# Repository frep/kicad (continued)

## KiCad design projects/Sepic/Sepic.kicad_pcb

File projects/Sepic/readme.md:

Sepic
=====

A Single Ended Primary Inductance Converter based on the LT1370.

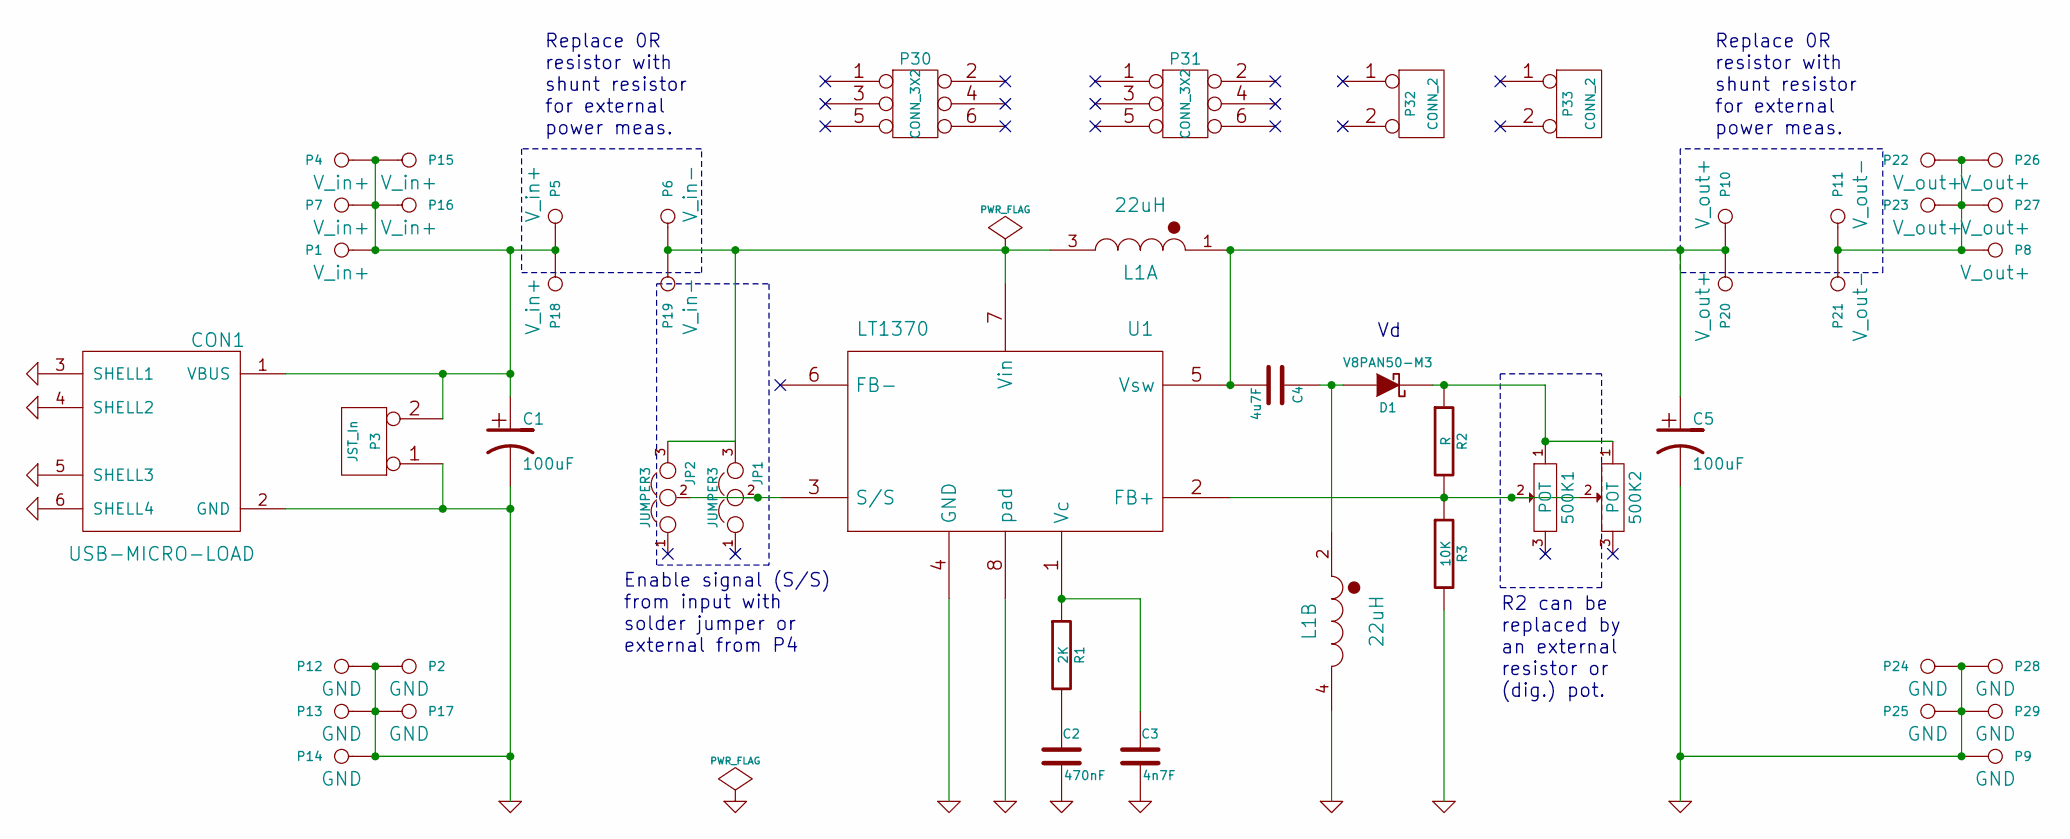
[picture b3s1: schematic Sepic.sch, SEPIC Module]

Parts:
500K1, 500K2: POT; Trimmer
C1, C5: 100uF; Cap_Nichicon
C2: 470nF; C0805
C3: 4n7F; C0805
C4: 4u7F; R1206
CON1: USB-MICRO-LOAD; USB_Micro_Load
D1: V8PAN50-M3; DO-221BC
JP1, JP2: JUMPER3; Pin_Proto_Straight_1x03
L1: 22uH; InductorsCoupled
P1: V_in+; SMD_SOLDERPOINT
P2, P12, P13, P17, P24, P25, P28, P29: GND; Pin_Proto_Straight_1x01
P3: JST_In; JST-PH-2-THM-RA
P4, P5, P7, P15, P16, P18: V_in+; Pin_Proto_Straight_1x01
P6, P19: V_in-; Pin_Proto_Straight_1x01
P8: V_out+; SMD_SOLDERPOINT
P9, P14: GND; SMD_SOLDERPOINT
P10, P20, P22, P23, P26, P27: V_out+; Pin_Proto_Straight_1x01
P11, P21: V_out-; Pin_Proto_Straight_1x01
P30, P31: CONN_3X2; Pin_Proto_Straight_2x03
P32, P33: CONN_2; Pin_Proto_Straight_1x02
R1: 2K; R0805
R2: R; R0805
R3: 10K; R0805
U1: LT1370; TO-263-7

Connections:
GND: C1.2, C2.2, C3.2, C5.2, CON1.2 (GND), CON1.3 (SHELL1), CON1.4 (SHELL2), CON1.5 (SHELL3), CON1.6 (SHELL4), L1.4, P2.1, P3.1, P9.1, P12.1, P13.1, P14.1, P17.1, P24.1, P25.1, P28.1, P29.1, R3.2, U1.4 (GND), U1.8 (pad)
unnamed: 500K1.1, 500K2.1, D1.2 (K), R2.1
unnamed: 500K1.2, 500K2.2, R2.2, R3.1, U1.2 (FB+)
unnamed: C1.1, CON1.1 (VBUS), P1.1, P3.2 (PM), P4.1, P5.1, P7.1, P15.1, P16.1, P18.1
unnamed: C2.1, R1.2
unnamed: C3.1, R1.1, U1.1 (Vc)
unnamed: C4.1, D1.1 (A), L1.2
unnamed: C4.2, C5.1, L1.1, P10.1, P20.1, U1.5 (Vsw)
unnamed: JP1.2, JP2.2, U1.3 (S/S)
unnamed: JP1.3, JP2.3, L1.3, P6.1, P19.1, U1.7 (Vin)
unnamed: P8.1, P11.1, P21.1, P22.1, P23.1, P26.1, P27.1

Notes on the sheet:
Enable signal (S/S) from input with solder jumper or external from P4
R2 can be replaced by an external resistor or (dig.) pot.
Replace 0R resistor with shunt resistor for external power meas.

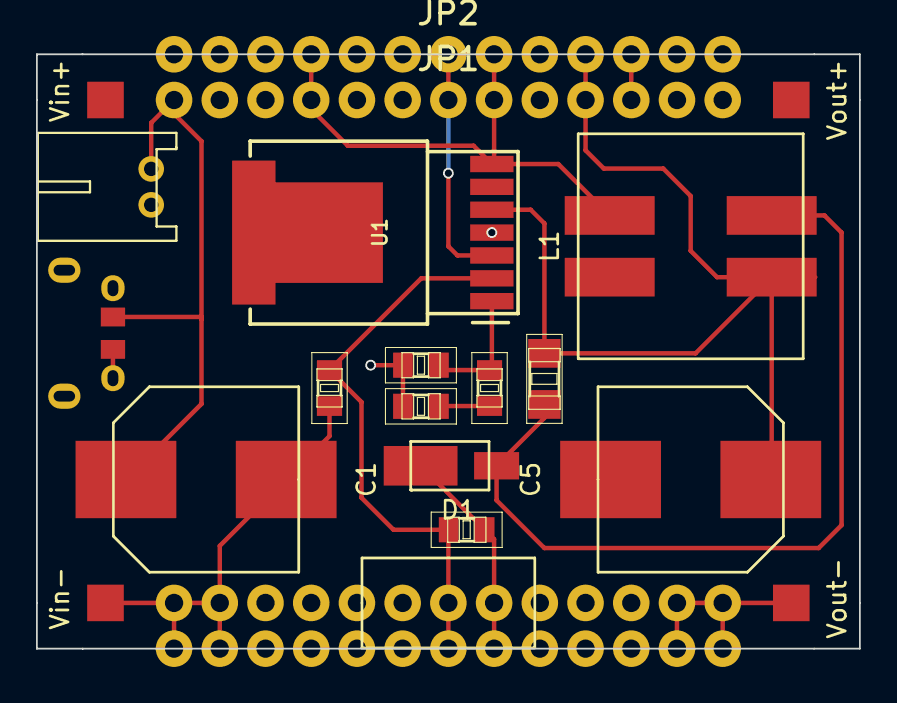
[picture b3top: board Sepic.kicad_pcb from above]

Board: 2 copper layers, 45.7 x 33.0 mm, 49 parts (0 on the bottom side), 11 nets.

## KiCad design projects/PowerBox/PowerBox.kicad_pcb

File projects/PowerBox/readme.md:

PowerBox
========
description is following soon...

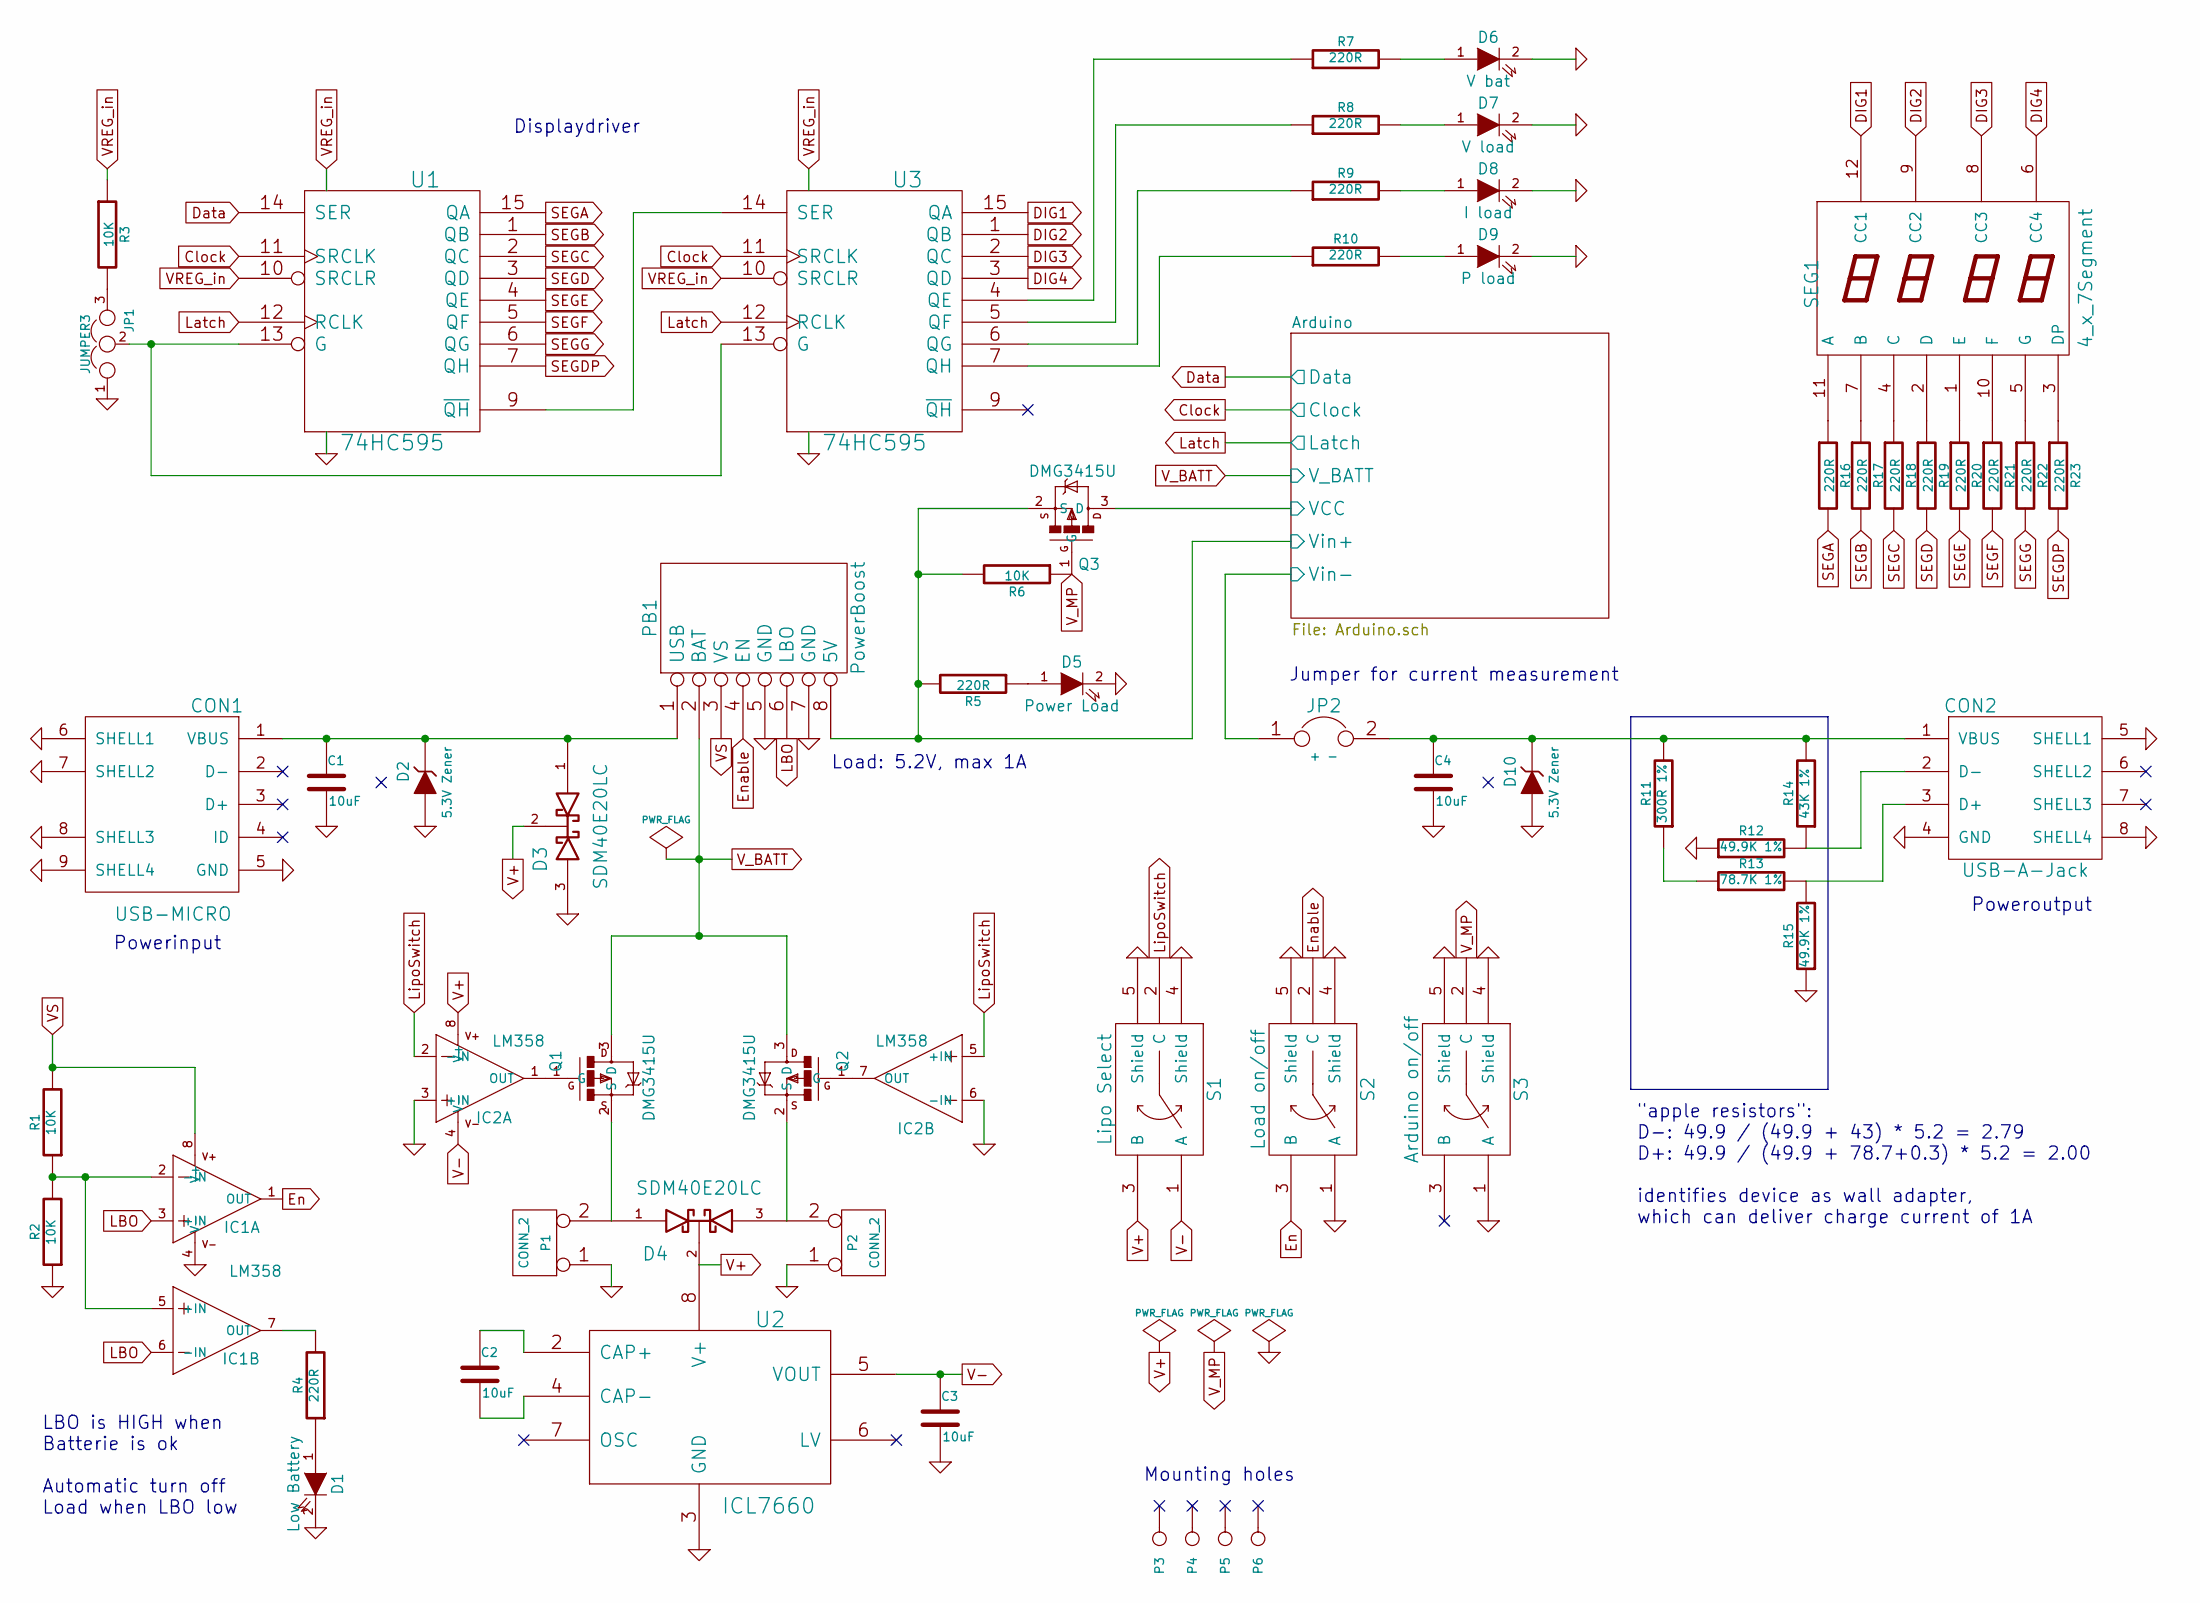
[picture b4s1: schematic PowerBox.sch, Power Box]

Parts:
C1, C2, C3, C4: 10uF; C0805
CON1: USB-MICRO; USB_Micro
CON2: USB-A-Jack
D1: Low Battery; LED-0805
D2, D10: 5.3V Zener; SOT23
D3, D4: SDM40E20LC; SOT23
D5: Power Load; LED-0805
D6: V bat; LED-0805
D7: V load; LED-0805
D8: I load; LED-0805
D9: P load; LED-0805
IC1, IC2: LM358; SOIC8
JP1: JUMPER3; Pin_Proto_Straight_1x03
JP2: + -; Pin_Proto_Straight_1x02
P1, P2: CONN_2; JST-PH-2-THM
P3, P4, P5, P6: CONN_1; MountingHole_3mm
PB1: PowerBoost; Powerboost1000C
Q1, Q2, Q3: DMG3415U; SOT23
R1, R2, R3, R6: 10K; R0805
R4, R5, R7, R8, R9, R10, R16, R17, R18, R19, R20, R21, R22, R23: 220R; R0805
R11: 300R 1%; R0805
R12, R15: 49.9K 1%; R0805
R13: 78.7K 1%; R0805
R14: 43K 1%; R0805
S1: Lipo Select; Switch_SPDT
S2: Load on/off; Switch_SPDT
S3: Arduino on/off; Switch_SPDT
SEG1: 4_x_7Segment; 4digit7segment
U1, U3: 74HC595; SO16
U2: ICL7660; SOIC8

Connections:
/Arduino/VCC: Q3.3 (D); also elsewhere on the board
/Arduino/Vin+: PB1.8 (5V), Q3.2 (S), R5.2, R6.2; also elsewhere on the board
/Arduino/Vin-: JP2.1; also elsewhere on the board
D7: U1.11 (SRCLK), U3.11 (SRCLK); also elsewhere on the board
DIG1: SEG1.12 (CC1), U3.15 (QA)
DIG2: SEG1.9 (CC2), U3.1 (QB)
DIG3: SEG1.8 (CC3), U3.2 (QC)
DIG4: SEG1.6 (CC4), U3.3 (QD)
En: IC1.1 (OUT), S2.3 (B)
Enable: PB1.4 (EN), S2.2 (C)
GND: C1.2, C3.2, C4.2, CON1.5 (GND), CON1.6 (SHELL1), CON1.7 (SHELL2), CON1.8 (SHELL3), CON1.9 (SHELL4), CON2.4 (GND), CON2.5 (SHELL1), CON2.8 (SHELL4), D1.2 (K), D2.1 (A), D3.3 (cathode), D5.2 (K), D6.2 (K), D7.2 (K), D8.2 (K), D9.2 (K), D10.1 (A), IC1.4 (V-), IC2.3 (+IN), IC2.6 (-IN), JP1.1, P1.1, P2.1, PB1.5 (GND), PB1.7 (GND), R2.1, R12.1, R15.1, S1.4 (Shield), S1.5 (Shield), S2.1 (A), S2.4 (Shield), S2.5 (Shield), S3.1 (A), S3.4 (Shield), S3.5 (Shield), U1.8 (GND), U2.3 (GND), U3.8 (GND); also elsewhere on the board
IO_11: U1.12 (RCLK), U3.12 (RCLK); also elsewhere on the board
IO_12: U1.14 (SER); also elsewhere on the board
LBO: IC1.3 (+IN), IC1.6 (-IN), PB1.6 (LBO)
LipoSwitch: IC2.2 (-IN), IC2.5 (+IN), S1.2 (C)
unnamed: C1.1, CON1.1 (VBUS), D2.3 (K), D3.1 (Anode), PB1.1 (USB)
unnamed: C2.1, U2.2 (CAP+)
unnamed: C2.2, U2.4 (CAP-)
unnamed: C4.1, CON2.1 (VBUS), D10.3 (K), JP2.2, R11.2, R14.2
unnamed: CON2.2 (D-), R12.2, R14.1
unnamed: CON2.3 (D+), R13.2, R15.2
unnamed: D1.1 (A), R4.1
unnamed: D4.1 (Anode), P1.2 (PM), Q1.2 (S)
unnamed: D4.3 (cathode), P2.2 (PM), Q2.2 (S)
unnamed: D5.1 (A), R5.1
unnamed: D6.1 (A), R7.2
unnamed: D7.1 (A), R8.2
unnamed: D8.1 (A), R9.2
unnamed: D9.1 (A), R10.2
unnamed: IC1.2 (-IN), IC1.5 (+IN), R1.1, R2.2
unnamed: IC1.7 (OUT), R4.2
unnamed: IC2.1 (OUT), Q1.1 (G)
unnamed: IC2.7 (OUT), Q2.1 (G)
unnamed: JP1.2, U1.13 (G), U3.13 (G)
unnamed: JP1.3, R3.2
unnamed: R7.1, U3.4 (QE)
unnamed: R8.1, U3.5 (QF)
unnamed: R9.1, U3.6 (QG)
unnamed: R10.1, U3.7 (QH)
unnamed: R11.1, R13.1
unnamed: R16.1, SEG1.11 (A)
unnamed: R17.1, SEG1.7 (B)
unnamed: R18.1, SEG1.4 (C)
unnamed: R19.1, SEG1.2 (D)
unnamed: R20.1, SEG1.1 (E)
unnamed: R21.1, SEG1.10 (F)
unnamed: R22.1, SEG1.5 (G)
unnamed: R23.1, SEG1.3 (DP)
unnamed: U1.9 (~QH), U3.14 (SER)
SEGA: R16.2, U1.15 (QA)
SEGB: R17.2, U1.1 (QB)
SEGC: R18.2, U1.2 (QC)
SEGD: R19.2, U1.3 (QD)
SEGDP: R23.2, U1.7 (QH)
SEGE: R20.2, U1.4 (QE)
SEGF: R21.2, U1.5 (QF)
SEGG: R22.2, U1.6 (QG)
V+: D3.2 (AK), D4.2 (AK), IC2.8 (V+), S1.3 (B), U2.8 (V+)
V-: C3.1, IC2.4 (V-), S1.1 (A), U2.5 (VOUT)
VREG_in: R3.1, U1.10 (SRCLR), U1.16 (VCC), U3.10 (SRCLR), U3.16 (VCC); also elsewhere on the board
VS: IC1.8 (V+), PB1.3 (VS), R1.2
V_BATT: PB1.2 (BAT), Q1.3 (D), Q2.3 (D); also elsewhere on the board
V_MP: Q3.1 (G), R6.1, S3.2 (C)

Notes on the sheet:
Powerinput
Poweroutput
Mounting holes
"apple resistors": D-: 49.9 / (49.9 + 43) * 5.2 = 2.79 D+: 49.9 / (49.9 + 78.7+0.3) * 5.2 = 2.00 identifies device as wall adapter, which can deliver charge current of 1A
LBO is HIGH when Batterie is ok Automatic turn off Load when LBO low
Jumper for current measurement
Displaydriver
Load: 5.2V, max 1A

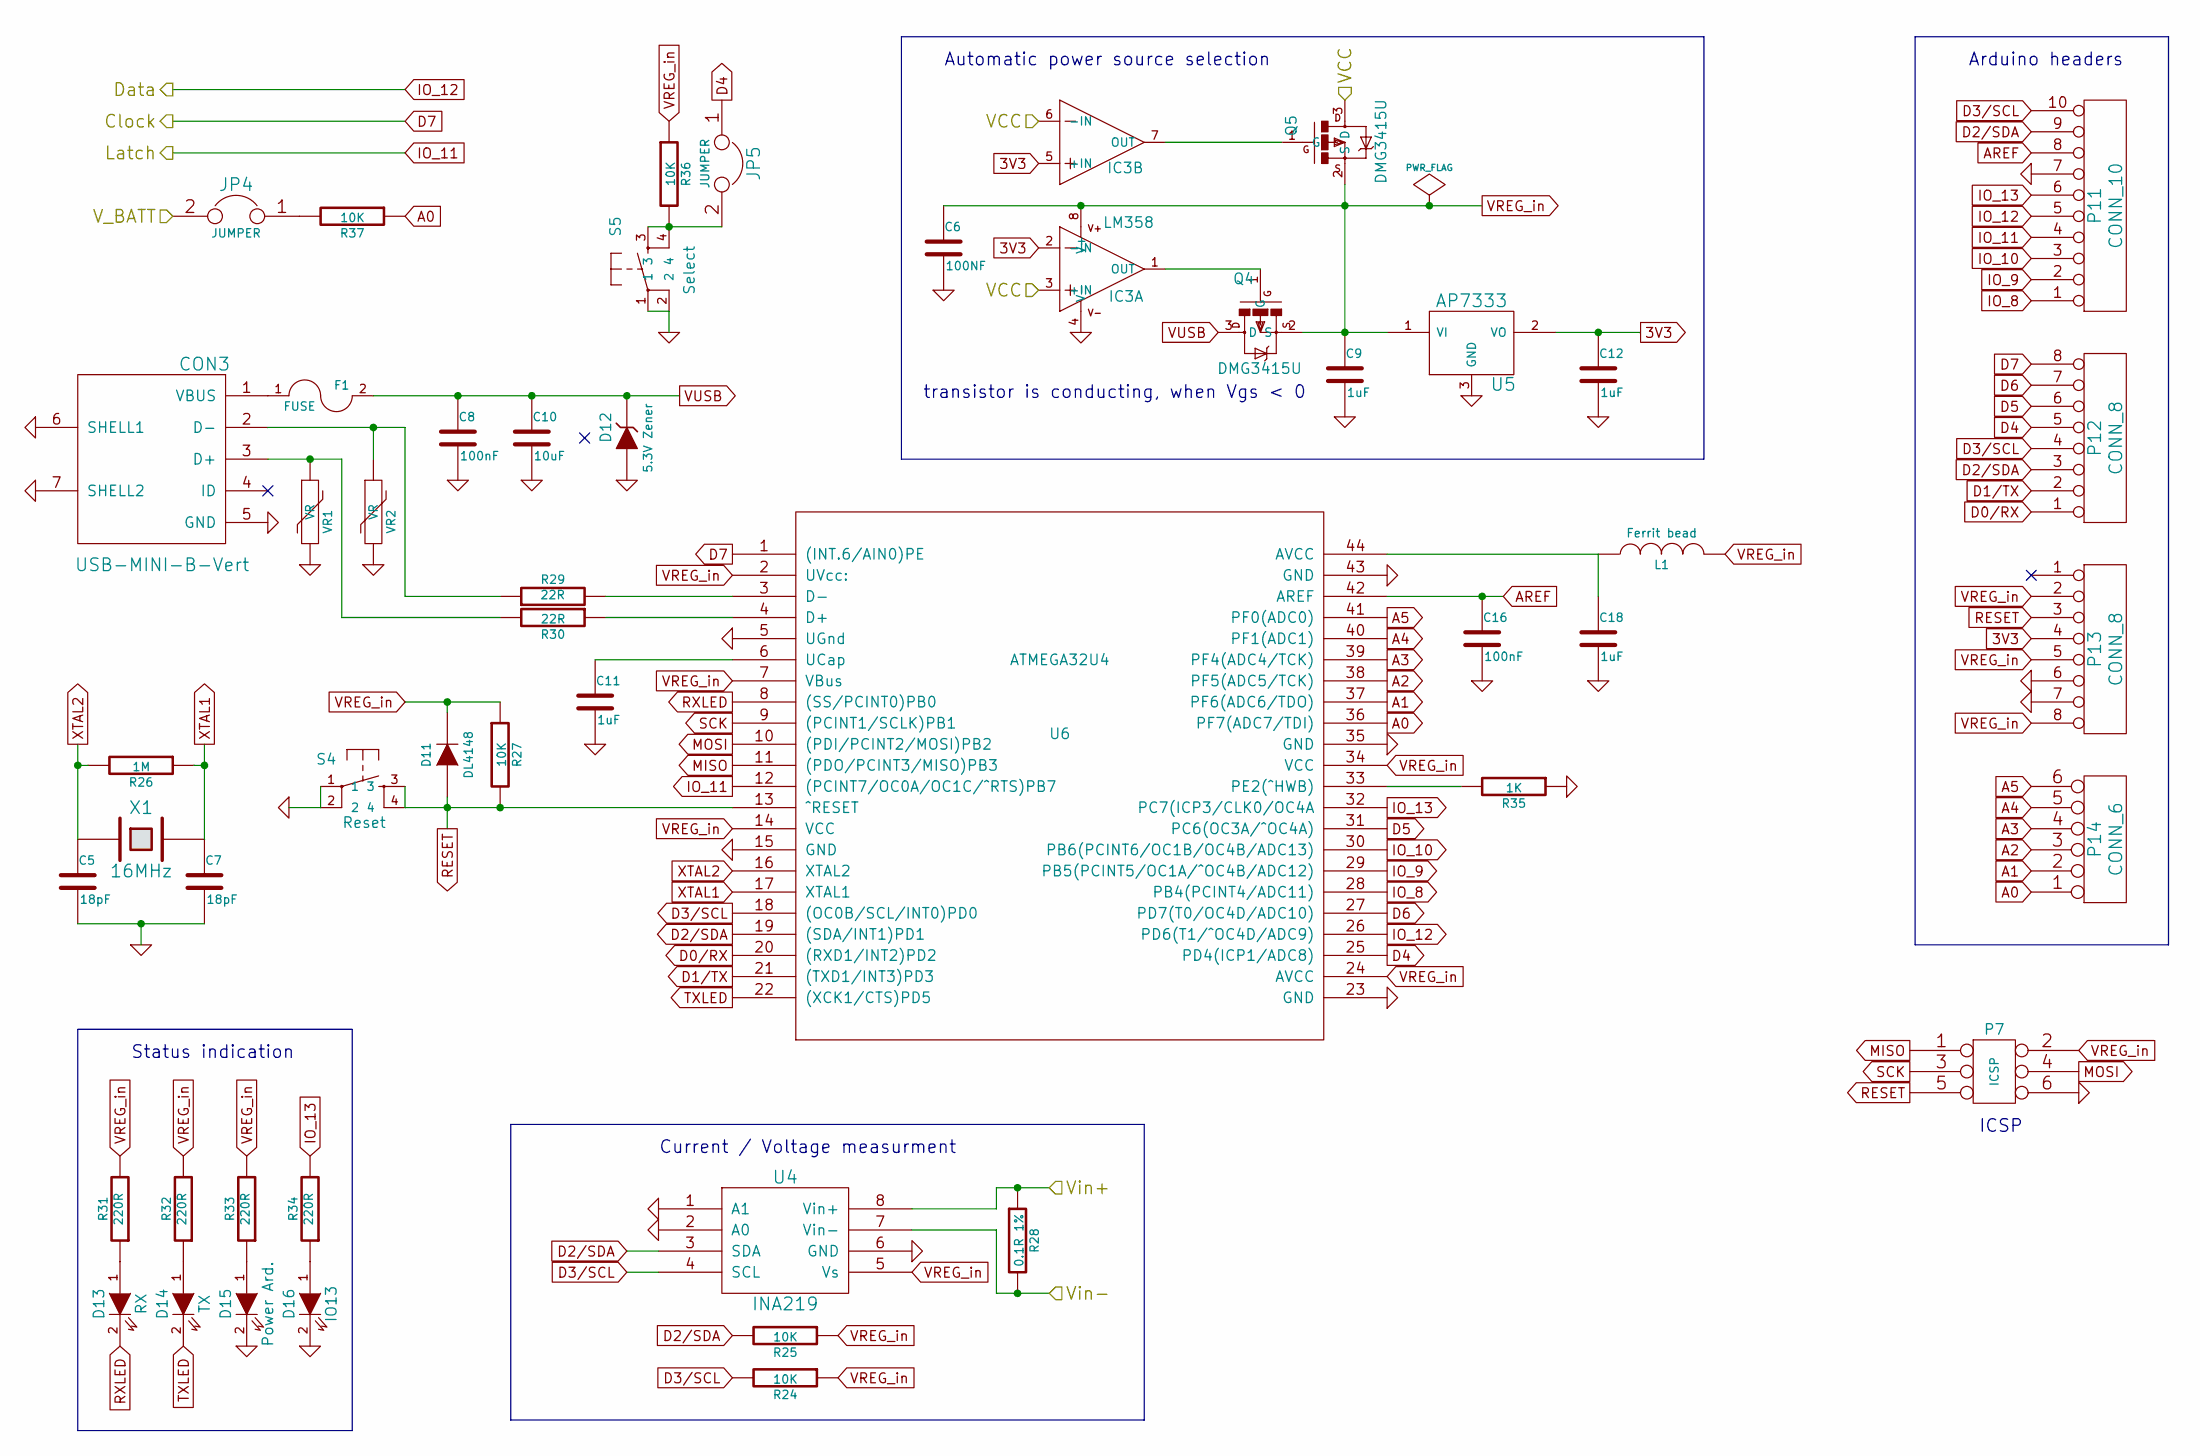
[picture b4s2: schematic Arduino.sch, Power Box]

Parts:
C5, C7: 18pF; C0805
C6: 100NF; C0805
C8, C16: 100nF; C0805
C9, C11, C12, C18: 1uF; C0805
C10: 10uF; C0805
CON3: USB-MINI-B-Vert; Vertical_USB_Mini_B
D11: DL4148; Diode-MiniMELF_Handsoldering
D12: 5.3V Zener; SOT23
D13: RX; LED-0805
D14: TX; LED-0805
D15: Power Ard.; LED-0805
D16: IO13; LED-0805
F1: FUSE; C1812
IC3: LM358; SOIC8
JP4, JP5: JUMPER; Pin_Proto_Straight_1x02
L1: Ferrit bead; R0805
P7: ICSP; Pin_Proto_Straight_2x03
P11: CONN_10; Pin_Header_Straight_1x10
P12, P13: CONN_8; Pin_Header_Straight_1x08
P14: CONN_6; Pin_Header_Straight_1x06
Q4, Q5: DMG3415U; SOT23
R24, R25, R27, R36, R37: 10K; R0805
R26: 1M; R0805
R28: 0.1R 1%; R1206
R29, R30: 22R; R0805
R31, R32, R33, R34: 220R; R0805
R35: 1K; R0805
S4: Reset; TACTILE-PTH
S5: Select; TACTILE-PTH
U4: INA219; SOIC8
U5: AP7333; SOT23
U6: ATMEGA32U4; TQFP44
VR1, VR2: VR; R0805
X1: 16MHz; HC49UP

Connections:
3V3: C12.1, IC3.2 (-IN), IC3.5 (+IN), P13.4, U5.2 (VO)
/Arduino/VCC: IC3.3 (+IN), IC3.6 (-IN), Q5.3 (D); also elsewhere on the board
/Arduino/Vin+: R28.1, U4.8 (Vin+); also elsewhere on the board
/Arduino/Vin-: R28.2, U4.7 (Vin-); also elsewhere on the board
A0: P14.1, R37.1, U6.36 (PF7(ADC7/TDI))
A1: P14.2, U6.37 (PF6(ADC6/TDO))
A2: P14.3, U6.38 (PF5(ADC5/TCK))
A3: P14.4, U6.39 (PF4(ADC4/TCK))
A4: P14.5, U6.40 (PF1(ADC1))
A5: P14.6, U6.41 (PF0(ADC0))
AREF: C16.1, P11.8, U6.42 (AREF)
D0/RX: P12.1, U6.20 ((RXD1/INT2)PD2)
D1/TX: P12.2, U6.21 ((TXD1/INT3)PD3)
D2/SDA: P11.9, P12.3, R25.2, U4.3 (SDA), U6.19 ((SDA/INT1)PD1)
D3/SCL: P11.10, P12.4, R24.2, U4.4 (SCL), U6.18 ((OC0B/SCL/INT0)PD0)
D4: JP5.1, P12.5, U6.25 (PD4(ICP1/ADC8))
D5: P12.6, U6.31 (PC6(OC3A/^OC4A))
D6: P12.7, U6.27 (PD7(T0/OC4D/ADC10))
D7: P12.8, U6.1 ((INT.6/AIN0)PE); also elsewhere on the board
GND: C5.2, C6.2, C7.2, C8.2, C9.2, C10.2, C11.2, C12.2, C16.2, C18.2, CON3.5 (GND), CON3.6 (SHELL1), CON3.7 (SHELL2), D12.1 (A), D15.2 (K), D16.2 (K), IC3.4 (V-), P7.6, P11.7, P13.6, P13.7, R35.1, S4.1, S4.2, S5.1, S5.2, U4.1 (A1), U4.2 (A0), U4.6 (GND), U5.3 (GND), U6.5 (UGnd), U6.15 (GND), U6.23 (GND), U6.35 (GND), U6.43 (GND), VR1.2, VR2.2; also elsewhere on the board
IO_8: P11.1, U6.28 (PB4(PCINT4/ADC11))
IO_9: P11.2, U6.29 (PB5(PCINT5/OC1A/^OC4B/ADC12))
IO_10: P11.3, U6.30 (PB6(PCINT6/OC1B/OC4B/ADC13))
IO_11: P11.4, U6.12 ((PCINT7/OC0A/OC1C/^RTS)PB7); also elsewhere on the board
IO_12: P11.5, U6.26 (PD6(T1/^OC4D/ADC9)); also elsewhere on the board
IO_13: P11.6, R34.2, U6.32 (PC7(ICP3/CLK0/OC4A)
MISO: P7.1, U6.11 ((PDO/PCINT3/MISO)PB3)
MOSI: P7.4, U6.10 ((PDI/PCINT2/MOSI)PB2)
unnamed: C11.1, U6.6 (UCap)
unnamed: C18.1, L1.1, U6.44 (AVCC)
unnamed: CON3.1 (VBUS), F1.1
unnamed: CON3.2 (D-), R29.1, VR2.1
unnamed: CON3.3 (D+), R30.2, VR1.1
unnamed: D13.1 (A), R31.1
unnamed: D14.1 (A), R32.1
unnamed: D15.1 (A), R33.1
unnamed: D16.1 (A), R34.1
unnamed: IC3.1 (OUT), Q4.1 (G)
unnamed: IC3.7 (OUT), Q5.1 (G)
unnamed: JP4.1, R37.2
unnamed: JP5.2, R36.2, S5.3, S5.4
unnamed: R29.2, U6.3 (D-)
unnamed: R30.1, U6.4 (D+)
unnamed: R35.2, U6.33 (PE2(^HWB))
RESET: D11.1 (A), P7.5, P13.3, R27.2, S4.3, S4.4, U6.13 (^RESET)
RXLED: D13.2 (K), U6.8 ((SS/PCINT0)PB0)
SCK: P7.3, U6.9 ((PCINT1/SCLK)PB1)
TXLED: D14.2 (K), U6.22 ((XCK1/CTS)PD5)
VREG_in: C6.1, C9.1, D11.2 (K), IC3.8 (V+), L1.2, P7.2, P13.2, P13.5, P13.8, Q4.2 (S), Q5.2 (S), R24.1, R25.1, R27.1, R31.2, R32.2, R33.2, R36.1, U4.5 (Vs), U5.1 (VI), U6.2 (UVcc:), U6.7 (VBus), U6.14 (VCC), U6.24 (AVCC), U6.34 (VCC); also elsewhere on the board
VUSB: C8.1, C10.1, D12.3 (K), F1.2, Q4.3 (D)
V_BATT: JP4.2; also elsewhere on the board
XTAL1: C7.1, R26.1, U6.17 (XTAL1), X1.2
XTAL2: C5.1, R26.2, U6.16 (XTAL2), X1.1

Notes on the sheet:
transistor is conducting, when Vgs < 0
Automatic power source selection
Arduino headers
ICSP
Current / Voltage measurment
Status indication

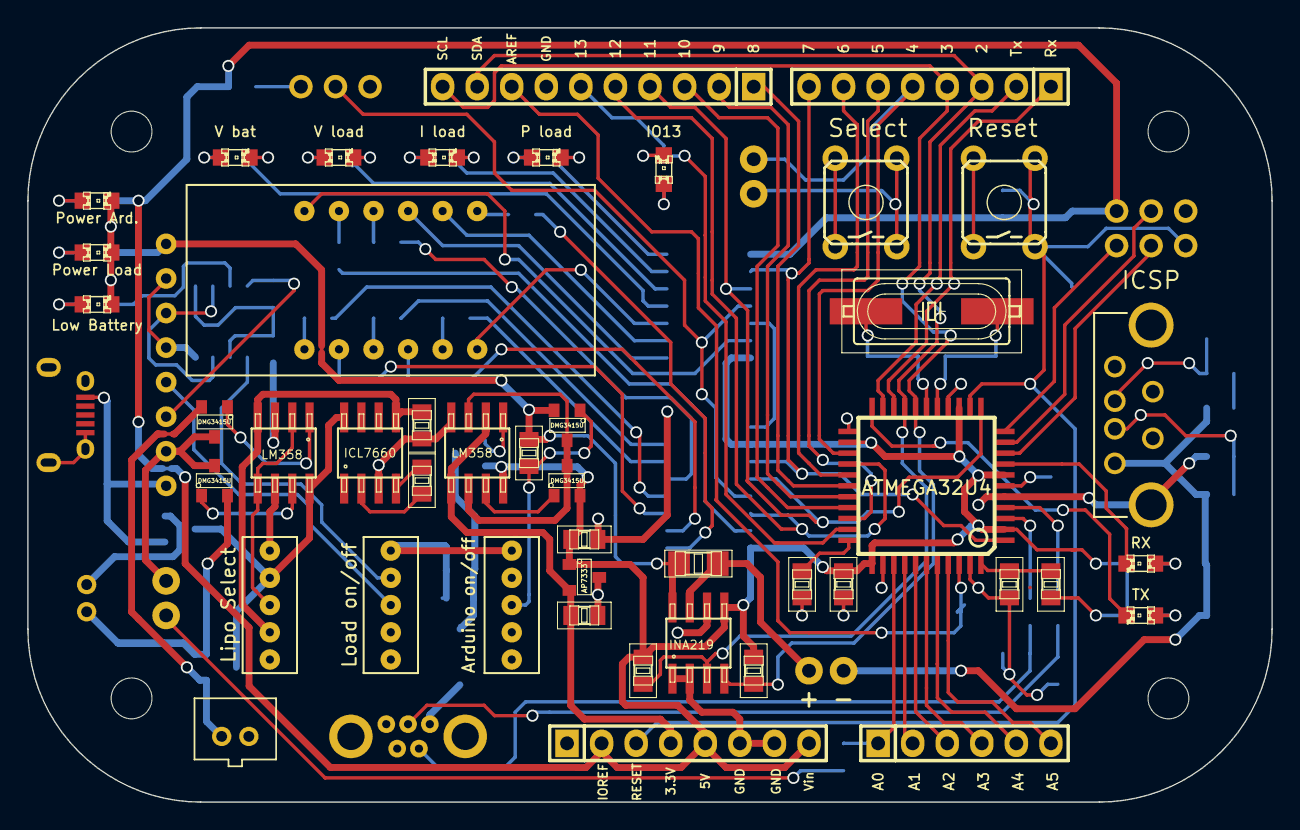
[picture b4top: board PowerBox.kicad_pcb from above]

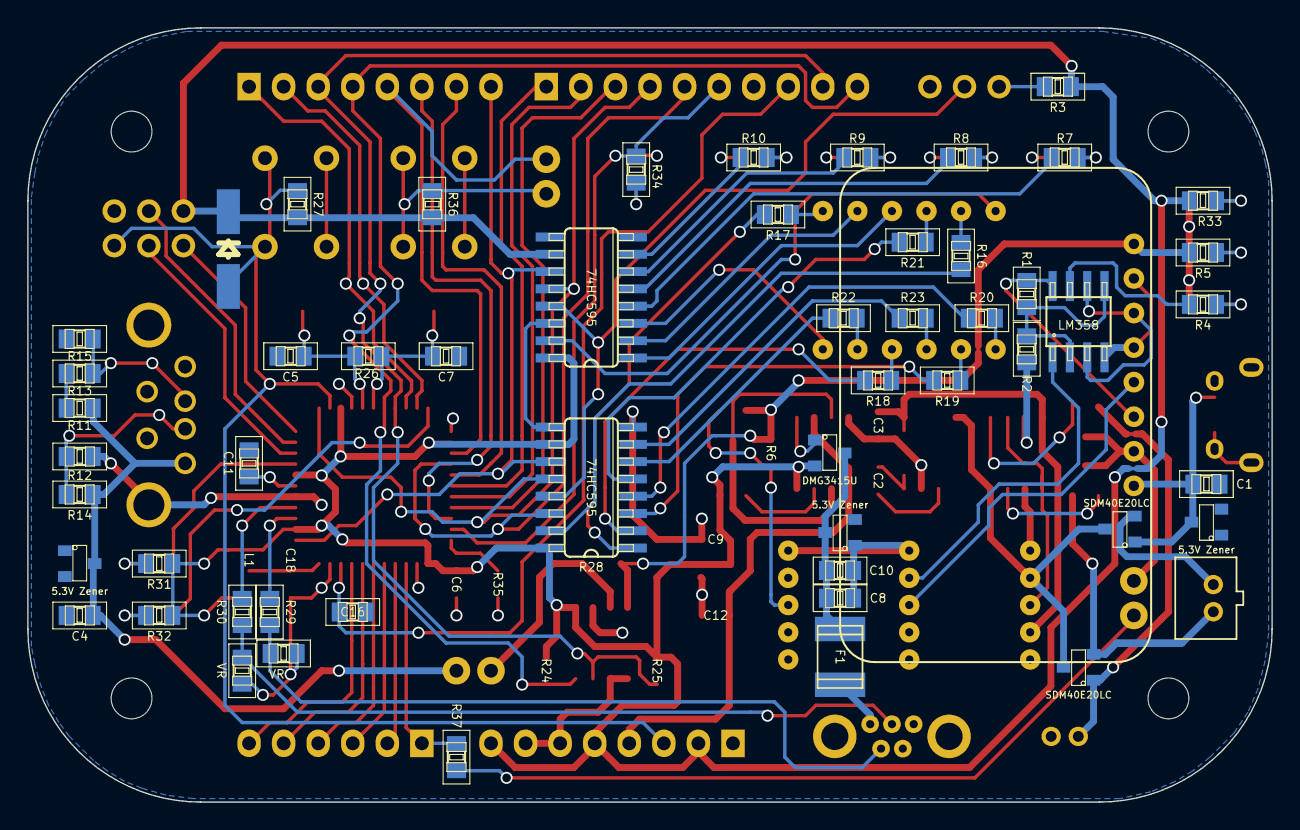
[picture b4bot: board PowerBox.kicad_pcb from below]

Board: 2 copper layers, 91.4 x 56.9 mm, 111 parts (55 on the bottom side), 107 nets.

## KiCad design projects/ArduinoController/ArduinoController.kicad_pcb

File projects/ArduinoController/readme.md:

Arduino Controller
==================
description is following soon...

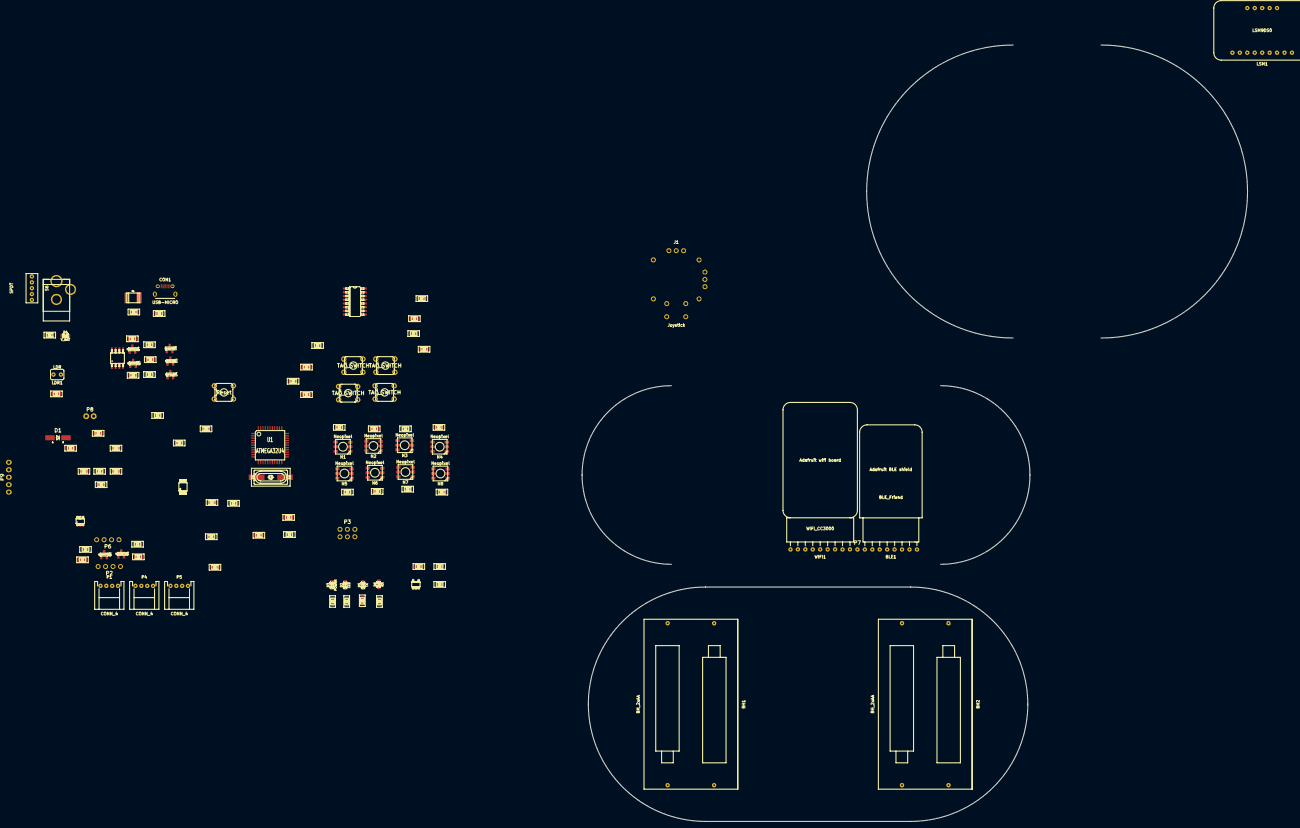
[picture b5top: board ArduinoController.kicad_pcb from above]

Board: 2 copper layers, 227.1 x 265.0 mm, 106 parts (0 on the bottom side), 74 nets, no tracks yet.

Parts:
BH1, BH2: BH_2xAA; Batterieholder_2xAA
BLE1: BLE_Friend; bluetooth_friend
C1, C2, C4, C15: 10nF; C0805
C3, C5: 18pF; C0805
C6, C7, C8, C9, C10, C11, C12, C13, C14, C16, C17, C19, C21, C27, C29: 100nF; C0805
C18, C24, C25, C26: 1uF; C0805
C20: 4.7uF; C0805
C22, C23, C28: 10uF; C0805
CN1: DCBARREL; DCJACK_2MM_PTH
CON1: USB-MICRO; USB_Micro
D1: DIODE; Diode-MiniMELF_Handsoldering
D2: LED; LED-0805
D3: POWER; LED-0805
D4: V_BAT; LED-0805
D5: TX; LED-0805
D6: RX; LED-0805
F1: FUSE; C1812
IC1: TMP36; SOT23-5L
IC2: LM358; SOIC8
J1: Joystick
L1: Ferrit Bead; R0805
LDR1: LDR
LSM1: LSM9DS0; lsm9ds0
N1, N2, N3, N4, N5, N6, N7, N8: Neopixel
P1, P4, P5: CONN_4; grove_con_angled
P2, P6: CONN_4; Pin_Proto_Straight_1x04
P3: CONN_3X2; Pin_Proto_Straight_2x03
P7: CONN_1; Pin_Proto_Straight_1x01
P8: CONN_2; Pin_Proto_Straight_1x02
P9: CONN_5; Pin_Header_Proto_1x05
Q1, Q2: MOSFET-N; SOT23
Q3, Q4: MOSFET-P; SOT23
R1, R2, R3, R4, R5, R6, R7, R8, R10, R13, R14, R15, R19: 10K; R0805
R9: 1M; R0805
R11, R12: 33; R0805
R16, R17: 1K; R0805
R18, R20, R21, R22, R23: 220; R0805
S1: Reset; TACTILE-PTH
S2, S3, S4, S5: TAC_SWITCH; TACTILE-PTH
S6: SPDT; Switch_SPDT
U1: ATMEGA32U4; TQFP44
U2: AD5274; MSOP10
U3: PCF8574; SO16
U4: NCP1117; SOT23
U5: MCP1700; SOT23
U6: ISL21070; SOT23
U7: MCP4716; SOT23-6
WIFI1: WIFI_CC3000; wifi_board
X1: 16MHz; HC49UP

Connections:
/Power/2V_Vcc: P9.3, U6.2, U7.6
/Power/5V_Vcc: BLE1.5, C7.1, C8.1, C9.1, C10.1, C11.1, C12.1, C13.1, C14.1, C16.2, C21.1, C24.1, C27.1, C28.1, D1.2, IC1.2, IC1.4, IC2.8, J1.1, J1.4, L1.2, LDR1.2, LSM1.1, N1.3, N1.5, N2.3, N2.5, N3.3, N3.5, N4.3, N4.5, N5.3, N5.5, N6.3, N6.5, N7.3, N7.5, N8.3, N8.5, P1.3, P2.3, P3.2, P4.3, P5.3, P9.1, Q3.2, Q4.2, R1.2, R2.2, R3.1, R4.1, R5.2, R8.2, R10.2, R13.2, R14.2, R15.2, R20.2, R22.2, R23.2, U1.2, U1.7, U1.14, U1.24, U1.34, U2.1, U2.7, U2.10, U3.16, U5.3, WIFI1.3
/Power/Ard_D+: CON1.3, R12.2
/Power/Ard_D-: CON1.2, R11.1
A0: C1.1, J1.2, U1.36
A1: C2.1, J1.5, U1.37
A2: C15.1, IC1.1, R16.2, U1.38
A3: LDR1.1, R19.2, U1.39
A4: P4.1, U1.40
A5: P4.2, U1.41
Batt_5V: C23.1, IC2.3, IC2.6, Q4.3, R21.1, U4.2
D0/RX: BLE1.3, U1.20
D1/TX: BLE1.4, U1.21
D2/SDA: LSM1.5, P1.2, P2.2, Q2.3, R1.1, R4.2, U1.19, U2.8, U3.15, U7.4
D3/SCL: LSM1.4, P1.1, P2.1, Q1.3, R2.1, R3.2, U1.18, U2.9, U3.14, U7.5
D4: U1.25, WIFI1.7
D5: U1.31, WIFI1.8
D6: P5.1, U1.27
D7: U1.1, WIFI1.9
GND: BH1.1, BLE1.2, BLE1.7, C1.2, C2.2, C3.2, C4.2, C5.2, C6.2, C7.2, C8.2, C9.2, C10.2, C11.2, C12.2, C13.2, C14.2, C15.2, C16.1, C17.2, C18.2, C19.2, C20.2, C21.2, C22.2, C23.2, C24.2, C25.2, C26.2, C27.2, C28.2, C29.2, CN1.GND, CN1.GNDB, CON1.5, CON1.6, CON1.7, CON1.8, CON1.9, D2.2, D3.2, D4.2, IC1.5, IC2.4, J1.3, J1.6, J1.9, LSM1.3, N1.6, N2.6, N3.6, N4.6, N5.6, N6.6, N7.6, N8.6, P1.4, P2.4, P3.6, P4.4, P5.4, P6.4, P9.5, R16.1, R17.1, R19.1, S1.1, S1.2, S2.1, S2.2, S3.1, S3.2, S4.1, S4.2, S5.1, S5.2, S6.4, S6.5, U1.5, U1.15, U1.23, U1.35, U1.43, U2.4, U2.6, U3.1, U3.2, U3.3, U3.8, U4.1, U5.1, U6.3, U7.2, WIFI1.1
IO_8: P5.2, U1.28
IO_9: N5.2, U1.29
IO_10: BLE1.8, U1.30
IO_11: BLE1.6, U1.12
IO_12: BLE1.1, U1.26
IO_13: R18.2, U1.32
MISO: P3.1, U1.11, WIFI1.5
MOSI: P3.4, U1.10, WIFI1.6
unnamed: BH1.2, BH1.3
unnamed: BH1.4, BH2.1
unnamed: BH2.2, BH2.3
unnamed: BH2.4, S6.1
unnamed: C3.1, R9.1, U1.16, X1.1
unnamed: C5.1, R9.2, U1.17, X1.2
unnamed: C6.1, U1.6
unnamed: C17.1, U1.42
unnamed: C18.1, L1.1, U1.44
unnamed: C26.1, U2.5
unnamed: CN1.PWR, S6.3
unnamed: CON1.1, F1.1
unnamed: D2.1, R18.1
unnamed: D3.1, R20.1
unnamed: D4.1, R21.2
unnamed: D5.1, R22.1
unnamed: D6.1, R23.1
unnamed: IC2.1, Q3.1
unnamed: IC2.7, Q4.1
unnamed: N1.1, N6.2
unnamed: N1.2, N5.1
unnamed: N2.1, N7.2
unnamed: N2.2, N6.1
unnamed: N3.1, N8.2
unnamed: N3.2, N7.1
unnamed: N4.2, N8.1
unnamed: P6.1, Q1.2, R6.2
unnamed: P6.2, Q2.2, R7.2
unnamed: P8.1, U2.3
unnamed: P8.2, U2.2
unnamed: P9.4, U7.1
unnamed: R11.2, U1.3
unnamed: R12.1, U1.4
unnamed: R17.2, U1.33
P0: R10.1, S2.3, S2.4, U3.4
P1: R13.1, S3.3, S3.4, U3.5
P2: R14.1, S4.3, S4.4, U3.6
P3: R15.1, S5.3, S5.4, U3.7
P4: C4.1, J1.7, R5.1, U3.9
RESET: D1.1, P3.5, R8.1, S1.3, S1.4, U1.13
RXLED: D6.2, U1.8
SCK: P3.3, U1.9, WIFI1.4
TXLED: D5.2, U1.22
USB_5V: C19.1, C20.1, F1.2, Q3.3
VCC_3V3: C25.1, C29.1, IC2.2, IC2.5, P6.3, P9.2, Q1.1, Q2.1, R6.1, R7.1, U5.2, U6.1, U7.3
V_BATT: C22.1, S6.2, U4.3
